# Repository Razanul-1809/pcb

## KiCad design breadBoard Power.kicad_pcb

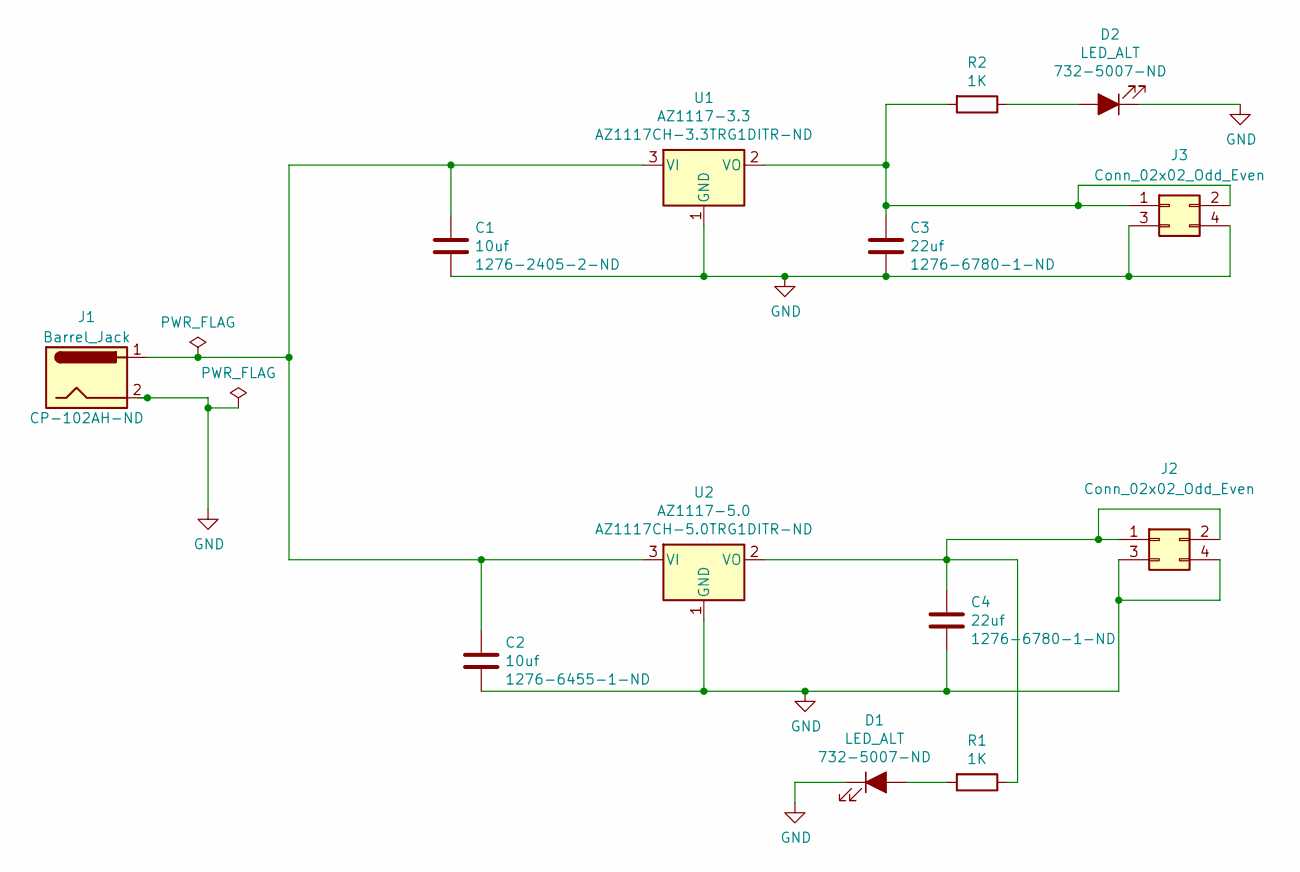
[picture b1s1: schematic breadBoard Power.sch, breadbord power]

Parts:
C1: 10uf; C_0805_2012Metric_Pad1.15x1.40mm_HandSolder; Digikey 1276-2405-2-ND
C2: 10uf; C_0805_2012Metric_Pad1.15x1.40mm_HandSolder; Digikey 1276-6455-1-ND
C3, C4: 22uf; C_0805_2012Metric_Pad1.15x1.40mm_HandSolder; Digikey 1276-6780-1-ND
D1, D2: LED_ALT; LED_D3.0mm; Digikey 732-5007-ND
J1: Barrel_Jack; BarrelJack_CUI_PJ-102AH_Horizontal; Digikey CP-102AH-ND
J2, J3: Conn_02x02_Odd_Even; PinHeader_2x02_P2.54mm_Vertical
R1, R2: 1K; R_0805_2012Metric_Pad1.15x1.40mm_HandSolder
U1: AZ1117-3.3; SOT-223-3_TabPin2; Digikey AZ1117CH-3.3TRG1DITR-ND
U2: AZ1117-5.0; SOT-223-3_TabPin2; Digikey AZ1117CH-5.0TRG1DITR-ND

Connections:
GND: C1.2, C2.2, C3.2, C4.2, D1.1 (K), D2.1 (K), J1.2, J2.3, J2.4, J3.3, J3.4, U1.1 (GND), U2.1 (GND)
unnamed: C1.1, C2.1, J1.1, U1.3 (VI), U2.3 (VI)
unnamed: C3.1, J3.1, J3.2, R2.2, U1.2 (VO)
unnamed: C4.1, J2.1, J2.2, R1.1, U2.2 (VO)
unnamed: D1.2 (A), R1.2
unnamed: D2.2 (A), R2.1

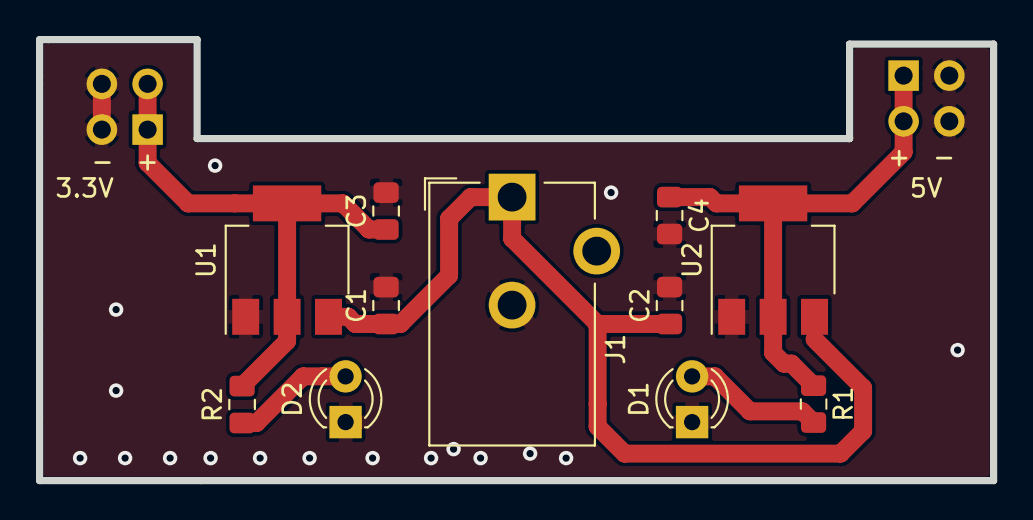
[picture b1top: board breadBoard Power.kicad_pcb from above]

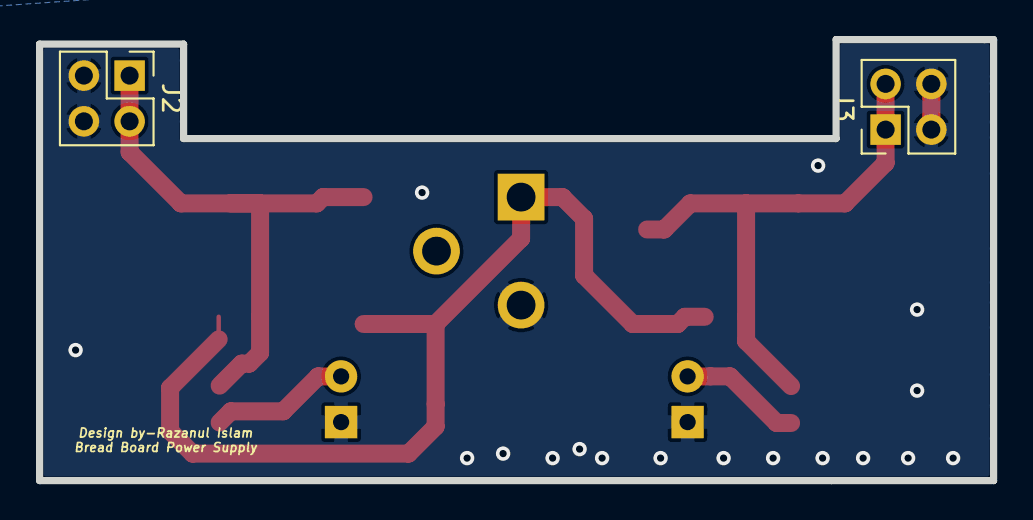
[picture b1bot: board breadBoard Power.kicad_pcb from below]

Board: 2 copper layers, 53.0 x 24.5 mm, 13 parts (2 on the bottom side), 6 nets.
